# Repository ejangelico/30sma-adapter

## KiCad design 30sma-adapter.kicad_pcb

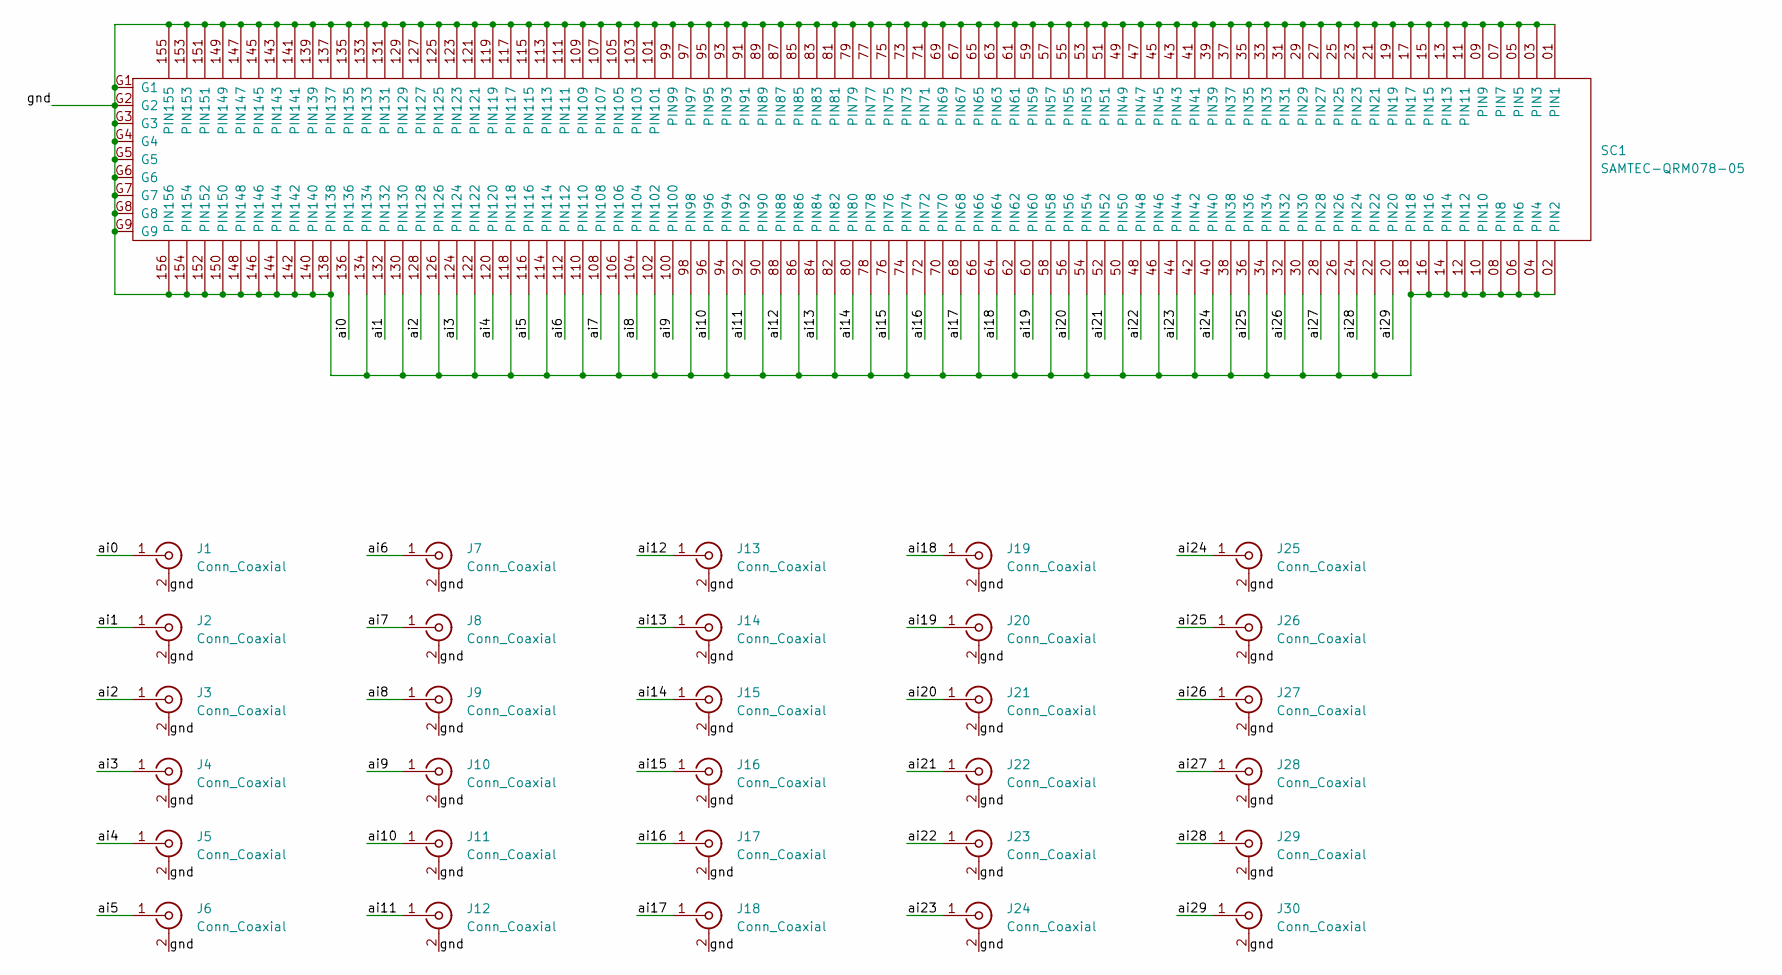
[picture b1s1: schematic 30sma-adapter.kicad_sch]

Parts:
J1, J2, J3, J4, J5, J6, J7, J8, J9, J10, J11, J12, J13, J14, J15, J16, J17, J18, J19, J20, J21, J22, J23, J24, J25, J26, J27, J28, J29, J30: Conn_Coaxial; SMA_Amphenol_132134_Vertical
SC1: SAMTEC-QRM078-05; SAMTEC_QRM8-078-05.0-L-D-A

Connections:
/ai0: J1.1 (In), SC1.136 (PIN136)
/ai1: J2.1 (In), SC1.132 (PIN132)
/ai2: J3.1 (In), SC1.128 (PIN128)
/ai3: J4.1 (In), SC1.124 (PIN124)
/ai4: J5.1 (In), SC1.120 (PIN120)
/ai5: J6.1 (In), SC1.116 (PIN116)
/ai6: J7.1 (In), SC1.112 (PIN112)
/ai7: J8.1 (In), SC1.108 (PIN108)
/ai8: J9.1 (In), SC1.104 (PIN104)
/ai9: J10.1 (In), SC1.100 (PIN100)
/ai10: J11.1 (In), SC1.96 (PIN96)
/ai11: J12.1 (In), SC1.92 (PIN92)
/ai12: J13.1 (In), SC1.88 (PIN88)
/ai13: J14.1 (In), SC1.84 (PIN84)
/ai14: J15.1 (In), SC1.80 (PIN80)
/ai15: J16.1 (In), SC1.76 (PIN76)
/ai16: J17.1 (In), SC1.72 (PIN72)
/ai17: J18.1 (In), SC1.68 (PIN68)
/ai18: J19.1 (In), SC1.64 (PIN64)
/ai19: J20.1 (In), SC1.60 (PIN60)
/ai20: J21.1 (In), SC1.56 (PIN56)
/ai21: J22.1 (In), SC1.52 (PIN52)
/ai22: J23.1 (In), SC1.48 (PIN48)
/ai23: J24.1 (In), SC1.44 (PIN44)
/ai24: J25.1 (In), SC1.40 (PIN40)
/ai25: J26.1 (In), SC1.36 (PIN36)
/ai26: J27.1 (In), SC1.32 (PIN32)
/ai27: J28.1 (In), SC1.28 (PIN28)
/ai28: J29.1 (In), SC1.24 (PIN24)
/ai29: J30.1 (In), SC1.20 (PIN20)
/gnd: J1.2 (Ext), J2.2 (Ext), J3.2 (Ext), J4.2 (Ext), J5.2 (Ext), J6.2 (Ext), J7.2 (Ext), J8.2 (Ext), J9.2 (Ext), J10.2 (Ext), J11.2 (Ext), J12.2 (Ext), J13.2 (Ext), J14.2 (Ext), J15.2 (Ext), J16.2 (Ext), J17.2 (Ext), J18.2 (Ext), J19.2 (Ext), J20.2 (Ext), J21.2 (Ext), J22.2 (Ext), J23.2 (Ext), J24.2 (Ext), J25.2 (Ext), J26.2 (Ext), J27.2 (Ext), J28.2 (Ext), J29.2 (Ext), J30.2 (Ext), SC1.01 (PIN1), SC1.02 (PIN2), SC1.03 (PIN3), SC1.04 (PIN4), SC1.05 (PIN5), SC1.06 (PIN6), SC1.07 (PIN7), SC1.08 (PIN8), SC1.09 (PIN9), SC1.10 (PIN10), SC1.11 (PIN11), SC1.12 (PIN12), SC1.13 (PIN13), SC1.14 (PIN14), SC1.15 (PIN15), SC1.16 (PIN16), SC1.17 (PIN17), SC1.18 (PIN18), SC1.19 (PIN19), SC1.21 (PIN21), SC1.22 (PIN22), SC1.23 (PIN23), SC1.25 (PIN25), SC1.26 (PIN26), SC1.27 (PIN27), SC1.29 (PIN29), SC1.30 (PIN30), SC1.31 (PIN31), SC1.33 (PIN33), SC1.34 (PIN34), SC1.35 (PIN35), SC1.37 (PIN37), SC1.38 (PIN38), SC1.39 (PIN39), SC1.41 (PIN41), SC1.42 (PIN42), SC1.43 (PIN43), SC1.45 (PIN45), SC1.46 (PIN46), SC1.47 (PIN47), SC1.49 (PIN49), SC1.50 (PIN50), SC1.51 (PIN51), SC1.53 (PIN53), SC1.54 (PIN54), SC1.55 (PIN55), SC1.57 (PIN57), SC1.58 (PIN58), SC1.59 (PIN59), SC1.61 (PIN61), SC1.62 (PIN62), SC1.63 (PIN63), SC1.65 (PIN65), SC1.66 (PIN66), SC1.67 (PIN67), SC1.69 (PIN69), SC1.70 (PIN70), SC1.71 (PIN71), SC1.73 (PIN73), SC1.74 (PIN74), SC1.75 (PIN75), SC1.77 (PIN77), SC1.78 (PIN78), SC1.79 (PIN79), SC1.81 (PIN81), SC1.82 (PIN82), SC1.83 (PIN83), SC1.85 (PIN85), SC1.86 (PIN86), SC1.87 (PIN87), SC1.89 (PIN89), SC1.90 (PIN90), SC1.91 (PIN91), SC1.93 (PIN93), SC1.94 (PIN94), SC1.95 (PIN95), SC1.97 (PIN97), SC1.98 (PIN98), SC1.99 (PIN99), SC1.101 (PIN101), SC1.102 (PIN102), SC1.103 (PIN103), SC1.105 (PIN105), SC1.106 (PIN106), SC1.107 (PIN107), SC1.109 (PIN109), SC1.110 (PIN110), SC1.111 (PIN111), SC1.113 (PIN113), SC1.114 (PIN114), SC1.115 (PIN115), SC1.117 (PIN117), SC1.118 (PIN118), SC1.119 (PIN119), SC1.121 (PIN121), SC1.122 (PIN122), SC1.123 (PIN123), SC1.125 (PIN125), SC1.126 (PIN126), SC1.127 (PIN127), SC1.129 (PIN129), SC1.130 (PIN130), SC1.131 (PIN131), SC1.133 (PIN133), SC1.134 (PIN134), SC1.135 (PIN135), SC1.137 (PIN137), SC1.138 (PIN138), SC1.139 (PIN139), SC1.140 (PIN140), SC1.141 (PIN141), SC1.142 (PIN142), SC1.143 (PIN143), SC1.144 (PIN144), SC1.145 (PIN145), SC1.146 (PIN146), SC1.147 (PIN147), SC1.148 (PIN148), SC1.149 (PIN149), SC1.150 (PIN150), SC1.151 (PIN151), SC1.152 (PIN152), SC1.153 (PIN153), SC1.154 (PIN154), SC1.155 (PIN155), SC1.156 (PIN156), SC1.G1, SC1.G2, SC1.G3, SC1.G4, SC1.G5, SC1.G6, SC1.G7, SC1.G8, SC1.G9

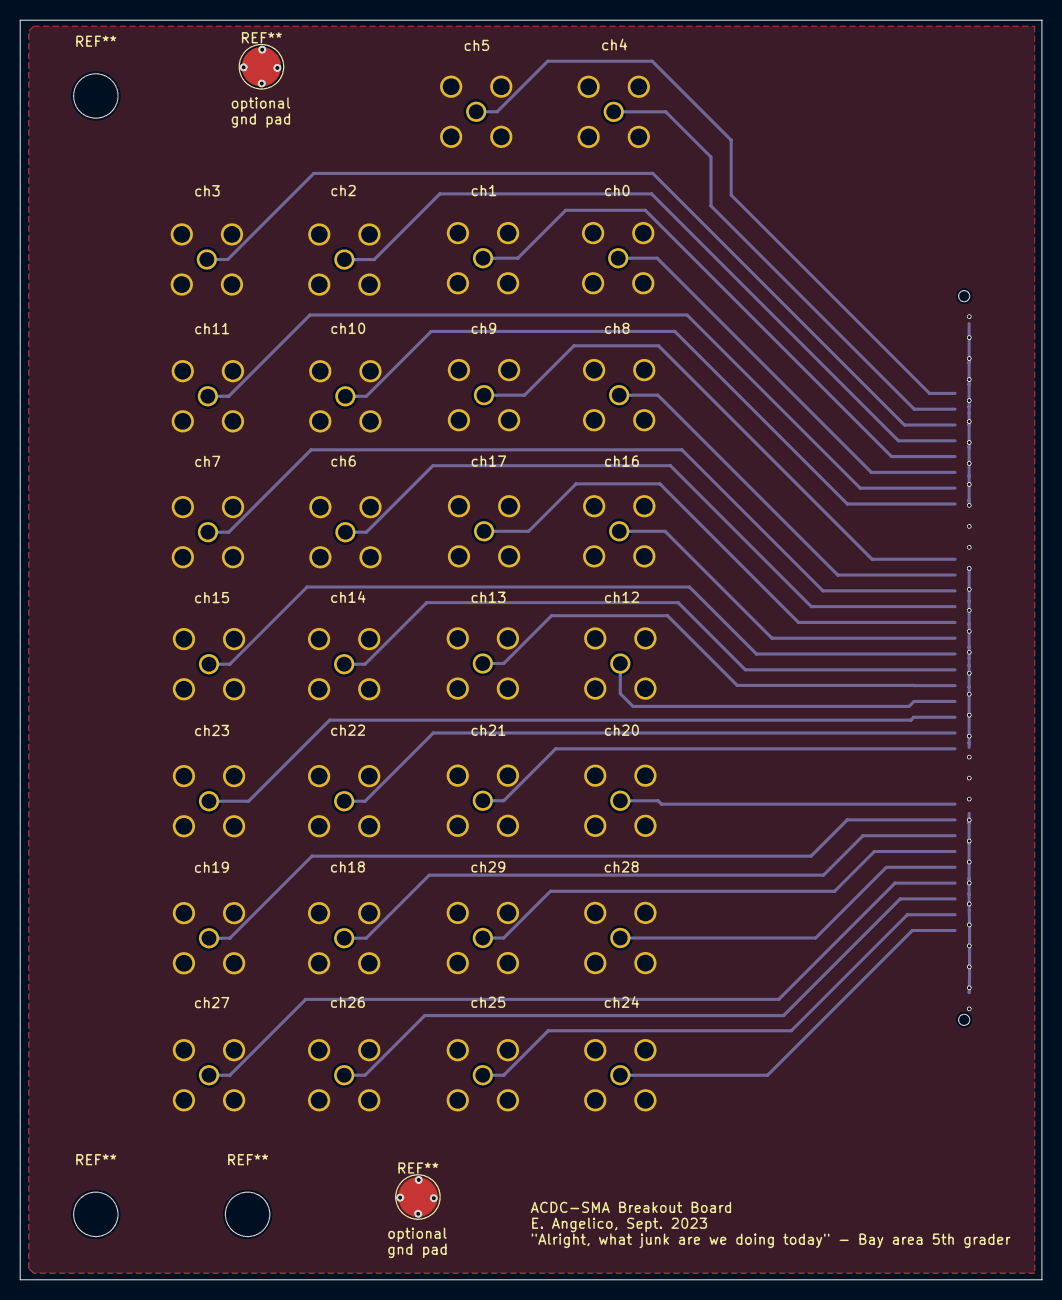
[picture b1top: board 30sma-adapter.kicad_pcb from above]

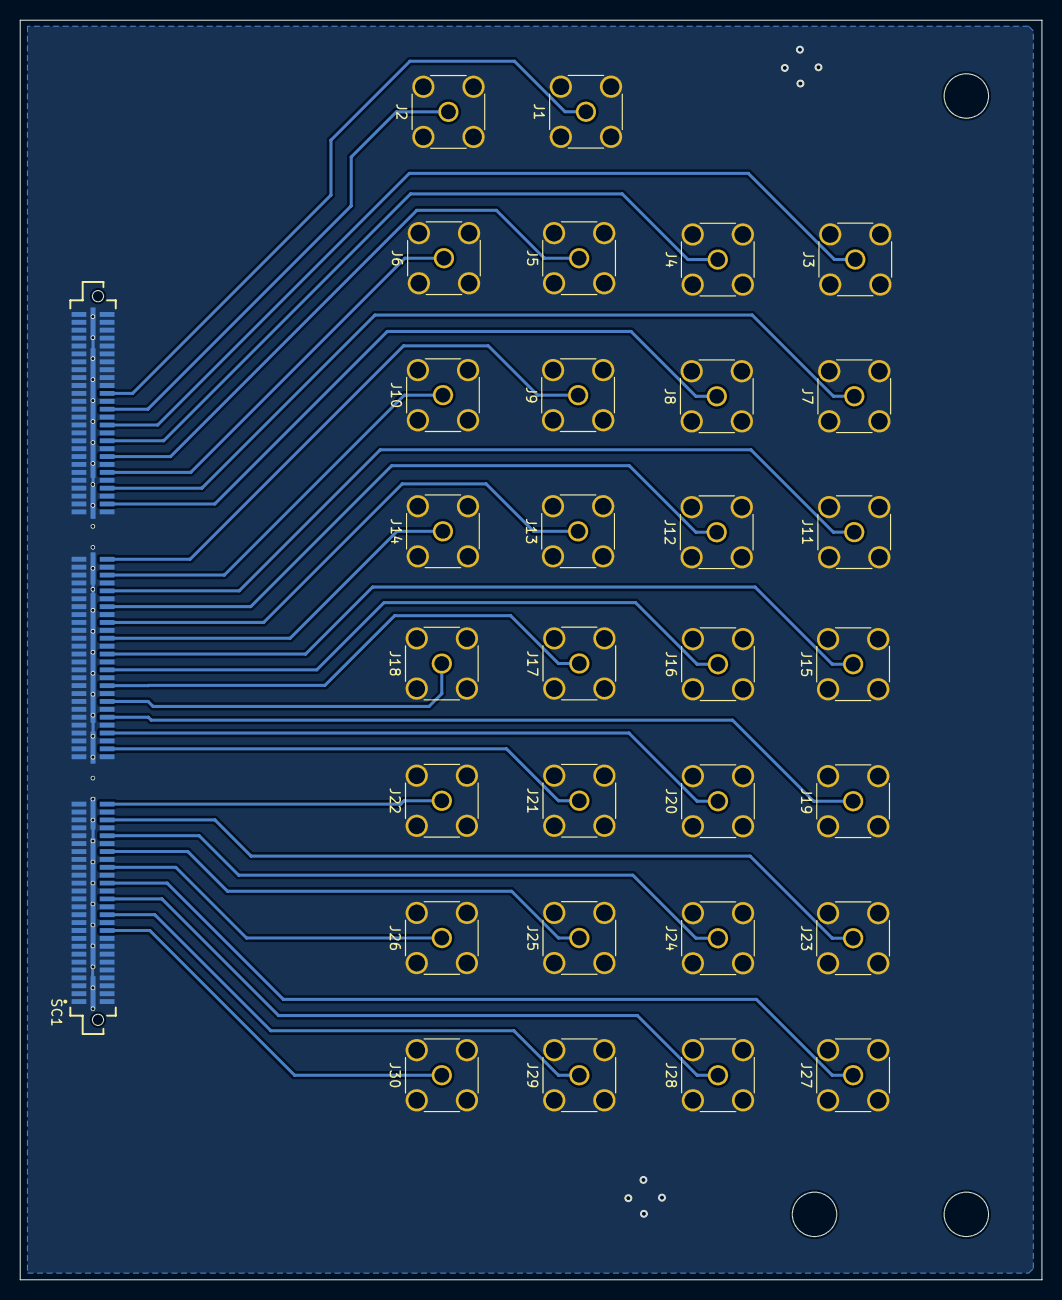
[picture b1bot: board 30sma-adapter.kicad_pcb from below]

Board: 4 copper layers, 103.5 x 127.6 mm, 31 parts (31 on the bottom side), 31 nets.

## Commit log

2023-09-15 First draft of full 30 SMA adapter to samtec male, intended to mate directly (with mounting holes for standoffs) to the ACDC rev C
2023-09-15 Added PDFs. Realized no edge cuts yet
2023-09-21 Relabeled silkscreen for the SMA channels to match the ACDC psec channels. Added edge cuts and other silk screening.
